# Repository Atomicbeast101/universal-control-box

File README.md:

# Universal Control Box

Kicad-designed universal control box PCB that provides the capability for end-users to quickly control various Home Assistant controls such as lights, covers, etc. The goal is to provide convenience for users to quickly make these changes without having to take out the phone to access Home Assistant app.

This design has gone through its third revision and hoping it would be the final version (updated as of 8/29/2024).

## Specifications

* Uses ESPHome to handle the turn knob and button events to trigger actions in Home Assistant.

## Schematic

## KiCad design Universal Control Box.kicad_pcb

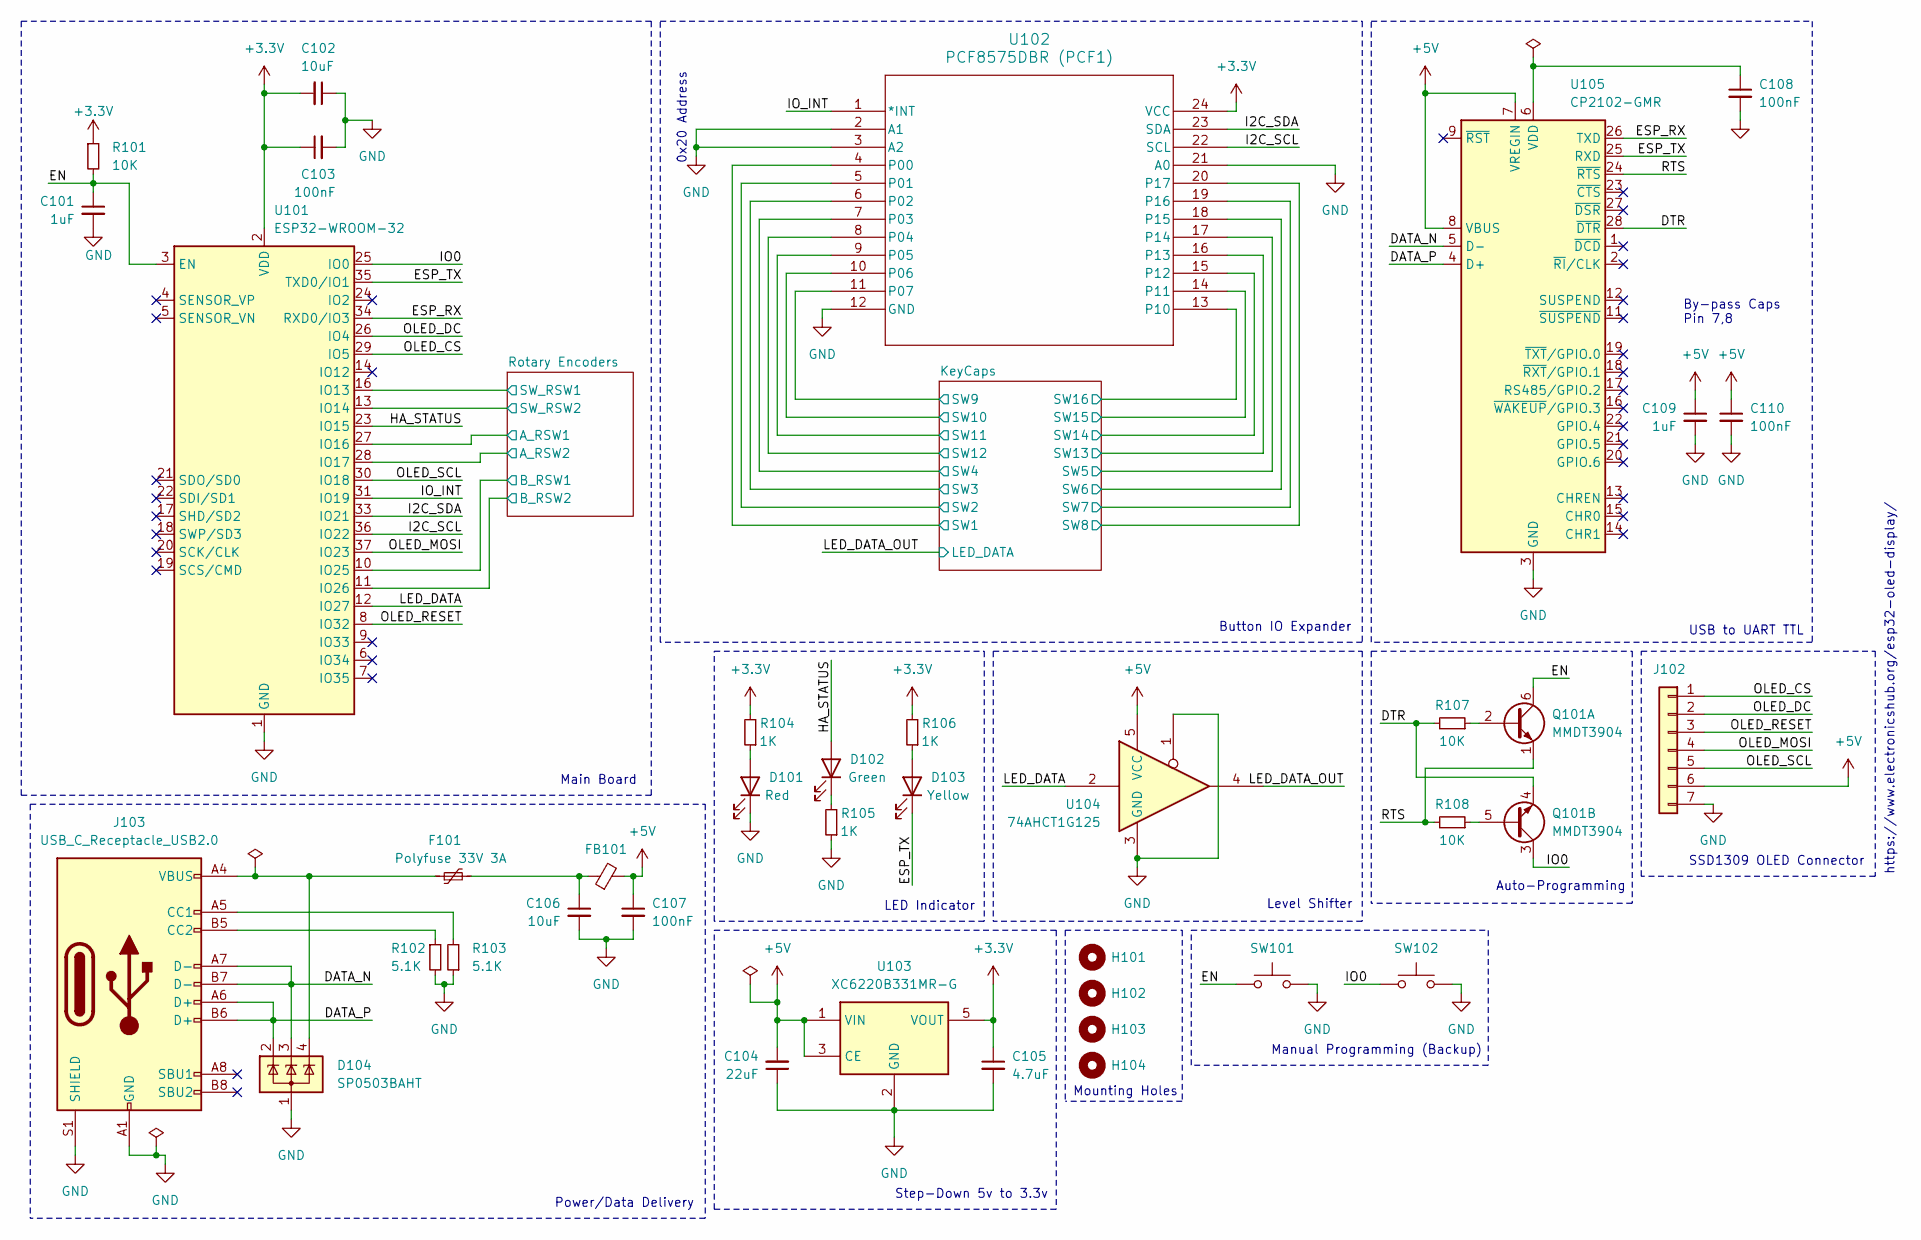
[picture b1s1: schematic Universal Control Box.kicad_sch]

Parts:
C101, C109: 1uF; C_0603_1608Metric; LCSC C14663
C102: 10uF; C_0603_1608Metric; LCSC C15850
C103, C107, C108, C110: 100nF; C_0603_1608Metric; LCSC C14663
C104: 22uF; C_0603_1608Metric; LCSC C59461
C105: 4.7uF; C_0603_1608Metric; LCSC C19666
C106: 10uF; C_0603_1608Metric; LCSC C96446
D101: Red; LED_0805_2012Metric; LCSC C84256
D102: Green; LED_0805_2012Metric; LCSC C2297
D103: Yellow; LED_0805_2012Metric; LCSC C2296
D104: SP0503BAHT; SOT-143; LCSC C7074
F101: Polyfuse 33V 3A; Fuse_1812_4532Metric; LCSC C883154
FB101: FerriteBead_Small; R_0805_2012Metric; LCSC C74487
H101, H102, H103, H104: MountingHole; MountingHole_3mm
J102: Conn_01x07; PinSocket_1x07_P2.54mm_Vertical_SSD1309
J103: USB_C_Receptacle_USB2.0; USB_C_Receptable_918-418K2023S40001; LCSC C2982555
Q101: MMDT3904; SOT-363_SC-70-6; LCSC C83572
R101, R107, R108: 10K; R_0603_1608Metric; LCSC C25804
R102, R103: 5.1K; R_0603_1608Metric; LCSC C25804
R104, R105, R106: 1K; R_0603_1608Metric; LCSC C21190
SW101, SW102: SW_Push; XKB-Connectivity-TS-1187A-B-A-B; LCSC C318884
U101: ESP32-WROOM-32; LCSC C473012
U102: PCF8575DBR (PCF1); TexasInstruments_PCF8575DBR; LCSC C2863388
U103: XC6220B331MR-G; SOT-23-5; LCSC C86534
U104: 74AHCT1G125; SOT-23-5; LCSC C7484
U105: CP2102-GMR; QFN-28-1EP_5x5mm_P0.5mm_EP3.35x3.35mm; LCSC C6568

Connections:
+3.3V: C102.2, C103.1, C105.1, R101.1, R104.2, R106.2, U101.2 (VDD), U102.24 (VCC), U103.5 (VOUT); also elsewhere on the board
+5V: C104.2, C107.1, C109.1, C110.1, FB101.2, J102.6, U103.1 (VIN), U103.3 (CE), U104.5 (VCC), U105.7 (VREGIN), U105.8 (VBUS); also elsewhere on the board
/DATA_N: D104.3 (K), J103.A7 (D-), J103.B7 (D-), U105.5 (D-)
/DATA_P: D104.2 (K), J103.A6 (D+), J103.B6 (D+), U105.4 (D+)
/DTR: Q101.4 (E2), R107.2, U105.28 (~DTR)
/EN: C101.1, Q101.6 (C1), R101.2, SW101.1, U101.3 (EN)
/ESP_RX: U101.34 (RXD0/IO3), U105.26 (TXD)
/ESP_TX: D103.1 (K), U101.35 (TXD0/IO1), U105.25 (RXD)
/HA_STATUS: D102.2 (A), U101.23 (IO15)
/I2C_SCL: U101.36 (IO22), U102.22 (SCL)
/I2C_SDA: U101.33 (IO21), U102.23 (SDA)
/IO0: Q101.3 (C2), SW102.1, U101.25 (IO0)
/IO_INT: U101.31 (IO19), U102.1 (*INT)
/KeyCaps/SW1: U102.4 (P00); also elsewhere on the board
/KeyCaps/SW2: U102.5 (P01); also elsewhere on the board
/KeyCaps/SW3: U102.6 (P02); also elsewhere on the board
/KeyCaps/SW4: U102.7 (P03); also elsewhere on the board
/KeyCaps/SW5: U102.17 (P14); also elsewhere on the board
/KeyCaps/SW6: U102.18 (P15); also elsewhere on the board
/KeyCaps/SW7: U102.19 (P16); also elsewhere on the board
/KeyCaps/SW8: U102.20 (P17); also elsewhere on the board
/KeyCaps/SW9: U102.11 (P07); also elsewhere on the board
/KeyCaps/SW10: U102.10 (P06); also elsewhere on the board
/KeyCaps/SW11: U102.9 (P05); also elsewhere on the board
/KeyCaps/SW12: U102.8 (P04); also elsewhere on the board
/KeyCaps/SW13: U102.16 (P13); also elsewhere on the board
/KeyCaps/SW14: U102.15 (P12); also elsewhere on the board
/KeyCaps/SW15: U102.14 (P11); also elsewhere on the board
/KeyCaps/SW16: U102.13 (P10); also elsewhere on the board
/LED_DATA: U101.12 (IO27), U104.2
/LED_DATA_OUT: U104.4; also elsewhere on the board
/OLED_CS: J102.1, U101.29 (IO5)
/OLED_DC: J102.2, U101.26 (IO4)
/OLED_MOSI: J102.4, U101.37 (IO23)
/OLED_RESET: J102.3, U101.8 (IO32)
/OLED_SCL: J102.5, U101.30 (IO18)
/RTS: Q101.1 (E1), R108.2, U105.24 (~RTS)
/Rotary Encoders/A_RSW1: U101.27 (IO16); also elsewhere on the board
/Rotary Encoders/A_RSW2: U101.28 (IO17); also elsewhere on the board
/Rotary Encoders/B_RSW1: U101.10 (IO25); also elsewhere on the board
/Rotary Encoders/B_RSW2: U101.11 (IO26); also elsewhere on the board
/Rotary Encoders/SW_RSW1: U101.16 (IO13); also elsewhere on the board
/Rotary Encoders/SW_RSW2: U101.13 (IO14); also elsewhere on the board
GND: C101.2, C102.1, C103.2, C104.1, C105.2, C106.2, C107.2, C108.2, C109.2, C110.2, D101.1 (K), D104.1 (A), J102.7, J103.A1 (GND), J103.A12 (GND), J103.B1 (GND), J103.B12 (GND), J103.S1 (SHIELD), R102.2, R103.1, R105.1, SW101.2, SW102.2, U101.1 (GND), U101.15 (GND), U101.38 (GND), U101.39 (GND), U102.2 (A1), U102.3 (A2), U102.12 (GND), U102.21 (A0), U103.2 (GND), U104.1, U104.3 (GND), U105.3 (GND), U105.29 (GND); also elsewhere on the board
unnamed: C106.1, F101.2, FB101.1
unnamed: D101.2 (A), R104.1
unnamed: D102.1 (K), R105.2
unnamed: D103.2 (A), R106.1
unnamed: D104.4 (K), F101.1, J103.A4 (VBUS), J103.A9 (VBUS), J103.B4 (VBUS), J103.B9 (VBUS)
unnamed: J103.A5 (CC1), R103.2
unnamed: J103.B5 (CC2), R102.1
unnamed: Q101.2 (B1), R107.1
unnamed: Q101.5 (B2), R108.1
unnamed: C108.1, U105.6 (VDD)

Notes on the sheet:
Mounting Holes
Power/Data Delivery
Button IO Expander
https://www.electronicshub.org/esp32-oled-display/
By-pass Caps Pin 7,8
Auto-Programming
LED Indicator
USB to UART TTL
0x20 Address
SSD1309 OLED Connector
Manual Programming (Backup)
Step-Down 5v to 3.3v
Level Shifter
Main Board

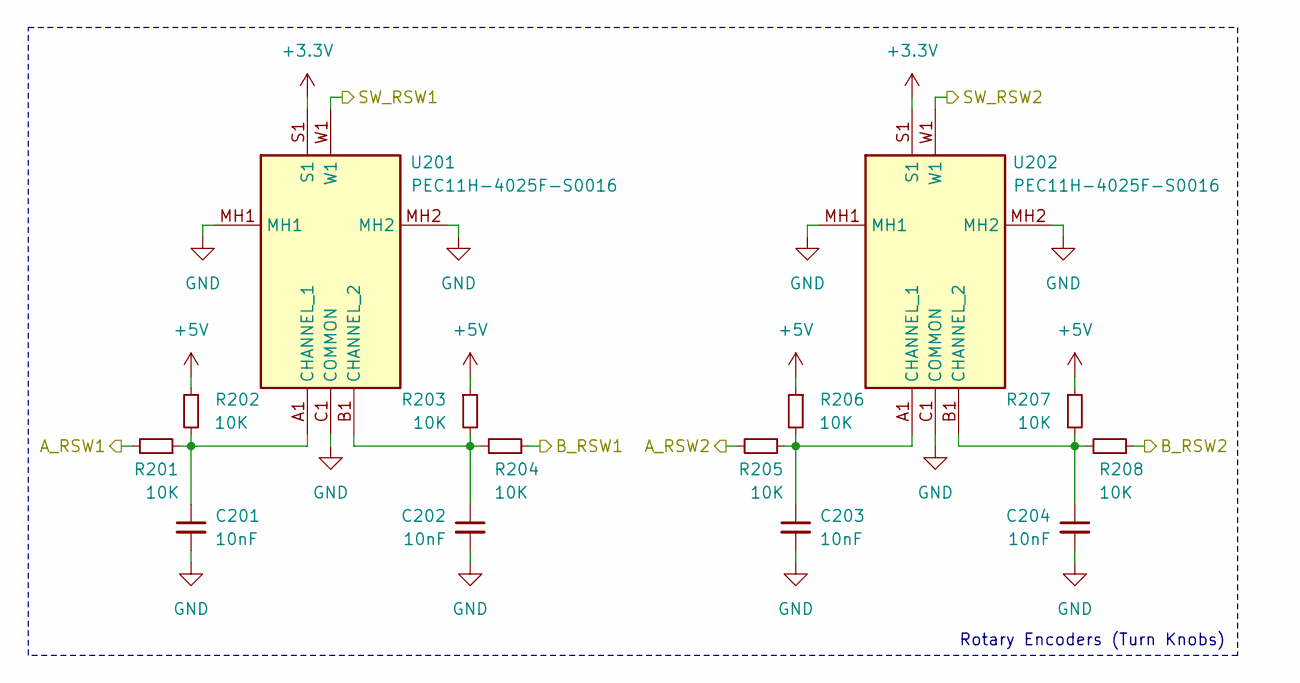
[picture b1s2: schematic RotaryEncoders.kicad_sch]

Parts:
C201, C202, C203, C204: 10nF; C_0603_1608Metric; LCSC C57112
R201, R202, R203, R204, R205, R206, R207, R208: 10K; R_0603_1608Metric; LCSC C25804
U201, U202: PEC11H-4025F-S0016; PEC11H4025FS0016; Mouser Part Number 652-PEC11H4025FS0016

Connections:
+3.3V: U201.S1, U202.S1; also elsewhere on the board
+5V: R202.1, R203.1, R206.1, R207.1; also elsewhere on the board
/Rotary Encoders/A_RSW1: R201.2; also elsewhere on the board
/Rotary Encoders/A_RSW2: R205.2; also elsewhere on the board
/Rotary Encoders/B_RSW1: R204.1; also elsewhere on the board
/Rotary Encoders/B_RSW2: R208.1; also elsewhere on the board
/Rotary Encoders/SW_RSW1: U201.W1; also elsewhere on the board
/Rotary Encoders/SW_RSW2: U202.W1; also elsewhere on the board
GND: C201.2, C202.2, C203.2, C204.2, U201.C1 (COMMON), U201.MH1, U201.MH2, U202.C1 (COMMON), U202.MH1, U202.MH2; also elsewhere on the board
unnamed: C201.1, R201.1, R202.2, U201.A1 (CHANNEL_1)
unnamed: C202.1, R203.2, R204.2, U201.B1 (CHANNEL_2)
unnamed: C203.1, R205.1, R206.2, U202.A1 (CHANNEL_1)
unnamed: C204.1, R207.2, R208.2, U202.B1 (CHANNEL_2)

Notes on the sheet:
Rotary Encoders (Turn Knobs)

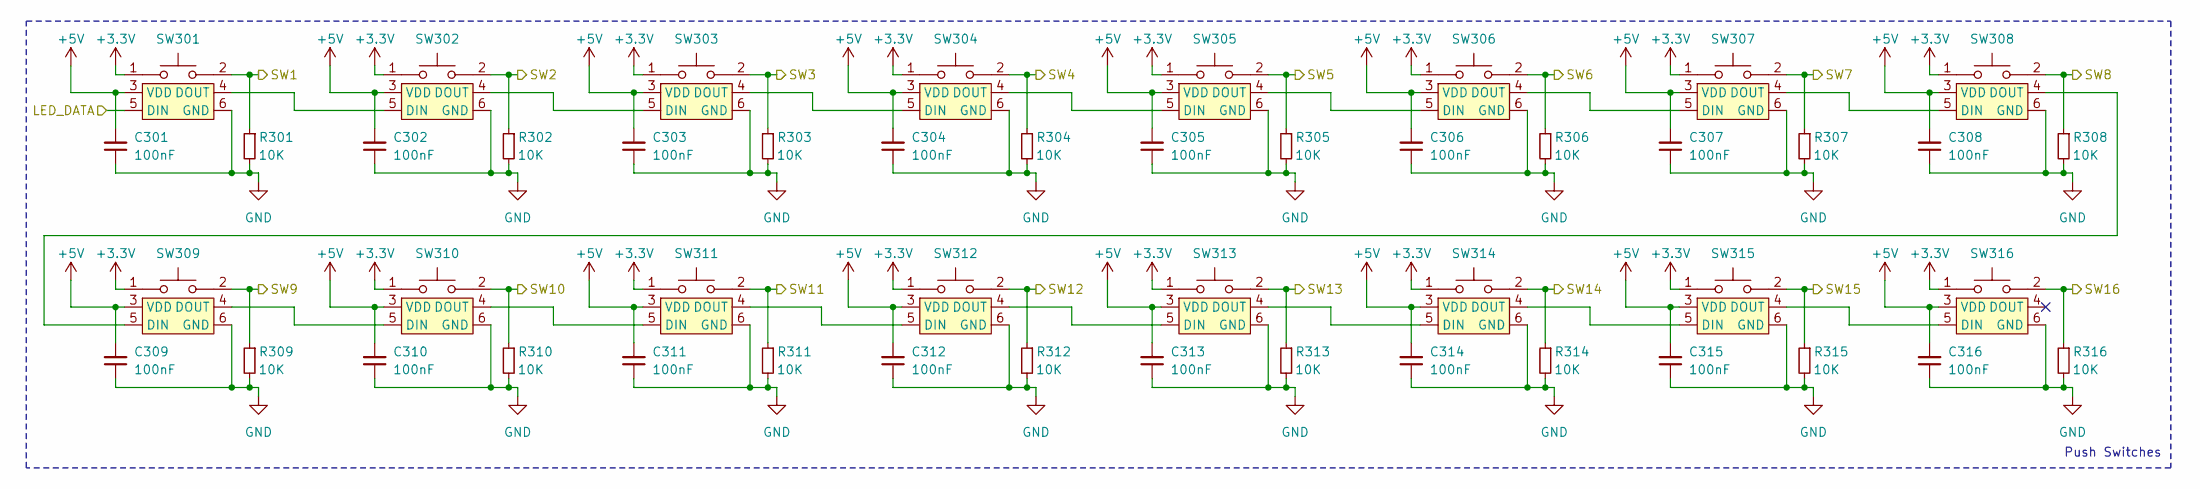
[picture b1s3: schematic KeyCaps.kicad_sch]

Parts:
C301, C302, C303, C304, C305, C306, C307, C308, C309, C310, C311, C312, C313, C314, C315, C316: 100nF; C_0603_1608Metric; LCSC C14663
R301, R302, R303, R304, R305, R306, R307, R308, R309, R310, R311, R312, R313, R314, R315, R316: 10K; R_0603_1608Metric; LCSC C25804
SW301, SW302, SW303, SW304, SW305, SW306, SW307, SW308, SW309, SW310, SW311, SW312, SW313, SW314, SW315, SW316: CherryMX_1.00u_PCB_WS2812B-2020; LCSC C965555

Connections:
+3.3V: SW301.1, SW302.1, SW303.1, SW304.1, SW305.1, SW306.1, SW307.1, SW308.1, SW309.1, SW310.1, SW311.1, SW312.1, SW313.1, SW314.1, SW315.1, SW316.1; also elsewhere on the board
+5V: C301.2, C302.2, C303.2, C304.2, C305.2, C306.2, C307.2, C308.2, C309.2, C310.2, C311.2, C312.2, C313.2, C314.2, C315.2, C316.2, SW301.3 (VDD), SW302.3 (VDD), SW303.3 (VDD), SW304.3 (VDD), SW305.3 (VDD), SW306.3 (VDD), SW307.3 (VDD), SW308.3 (VDD), SW309.3 (VDD), SW310.3 (VDD), SW311.3 (VDD), SW312.3 (VDD), SW313.3 (VDD), SW314.3 (VDD), SW315.3 (VDD), SW316.3 (VDD); also elsewhere on the board
/KeyCaps/SW1: R301.1, SW301.2; also elsewhere on the board
/KeyCaps/SW2: R302.1, SW302.2; also elsewhere on the board
/KeyCaps/SW3: R303.1, SW303.2; also elsewhere on the board
/KeyCaps/SW4: R304.1, SW304.2; also elsewhere on the board
/KeyCaps/SW5: R305.1, SW305.2; also elsewhere on the board
/KeyCaps/SW6: R306.1, SW306.2; also elsewhere on the board
/KeyCaps/SW7: R307.1, SW307.2; also elsewhere on the board
/KeyCaps/SW8: R308.1, SW308.2; also elsewhere on the board
/KeyCaps/SW9: R309.1, SW309.2; also elsewhere on the board
/KeyCaps/SW10: R310.1, SW310.2; also elsewhere on the board
/KeyCaps/SW11: R311.1, SW311.2; also elsewhere on the board
/KeyCaps/SW12: R312.1, SW312.2; also elsewhere on the board
/KeyCaps/SW13: R313.1, SW313.2; also elsewhere on the board
/KeyCaps/SW14: R314.1, SW314.2; also elsewhere on the board
/KeyCaps/SW15: R315.1, SW315.2; also elsewhere on the board
/KeyCaps/SW16: R316.1, SW316.2; also elsewhere on the board
/LED_DATA_OUT: SW301.5 (DIN); also elsewhere on the board
GND: C301.1, C302.1, C303.1, C304.1, C305.1, C306.1, C307.1, C308.1, C309.1, C310.1, C311.1, C312.1, C313.1, C314.1, C315.1, C316.1, R301.2, R302.2, R303.2, R304.2, R305.2, R306.2, R307.2, R308.2, R309.2, R310.2, R311.2, R312.2, R313.2, R314.2, R315.2, R316.2, SW301.6 (GND), SW302.6 (GND), SW303.6 (GND), SW304.6 (GND), SW305.6 (GND), SW306.6 (GND), SW307.6 (GND), SW308.6 (GND), SW309.6 (GND), SW310.6 (GND), SW311.6 (GND), SW312.6 (GND), SW313.6 (GND), SW314.6 (GND), SW315.6 (GND), SW316.6 (GND); also elsewhere on the board
unnamed: SW301.4 (DOUT), SW302.5 (DIN)
unnamed: SW302.4 (DOUT), SW303.5 (DIN)
unnamed: SW303.4 (DOUT), SW304.5 (DIN)
unnamed: SW304.4 (DOUT), SW305.5 (DIN)
unnamed: SW305.4 (DOUT), SW306.5 (DIN)
unnamed: SW306.4 (DOUT), SW307.5 (DIN)
unnamed: SW307.4 (DOUT), SW308.5 (DIN)
unnamed: SW308.4 (DOUT), SW309.5 (DIN)
unnamed: SW309.4 (DOUT), SW310.5 (DIN)
unnamed: SW310.4 (DOUT), SW311.5 (DIN)
unnamed: SW311.4 (DOUT), SW312.5 (DIN)
unnamed: SW312.4 (DOUT), SW313.5 (DIN)
unnamed: SW313.4 (DOUT), SW314.5 (DIN)
unnamed: SW314.4 (DOUT), SW315.5 (DIN)
unnamed: SW315.4 (DOUT), SW316.5 (DIN)

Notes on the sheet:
Push Switches

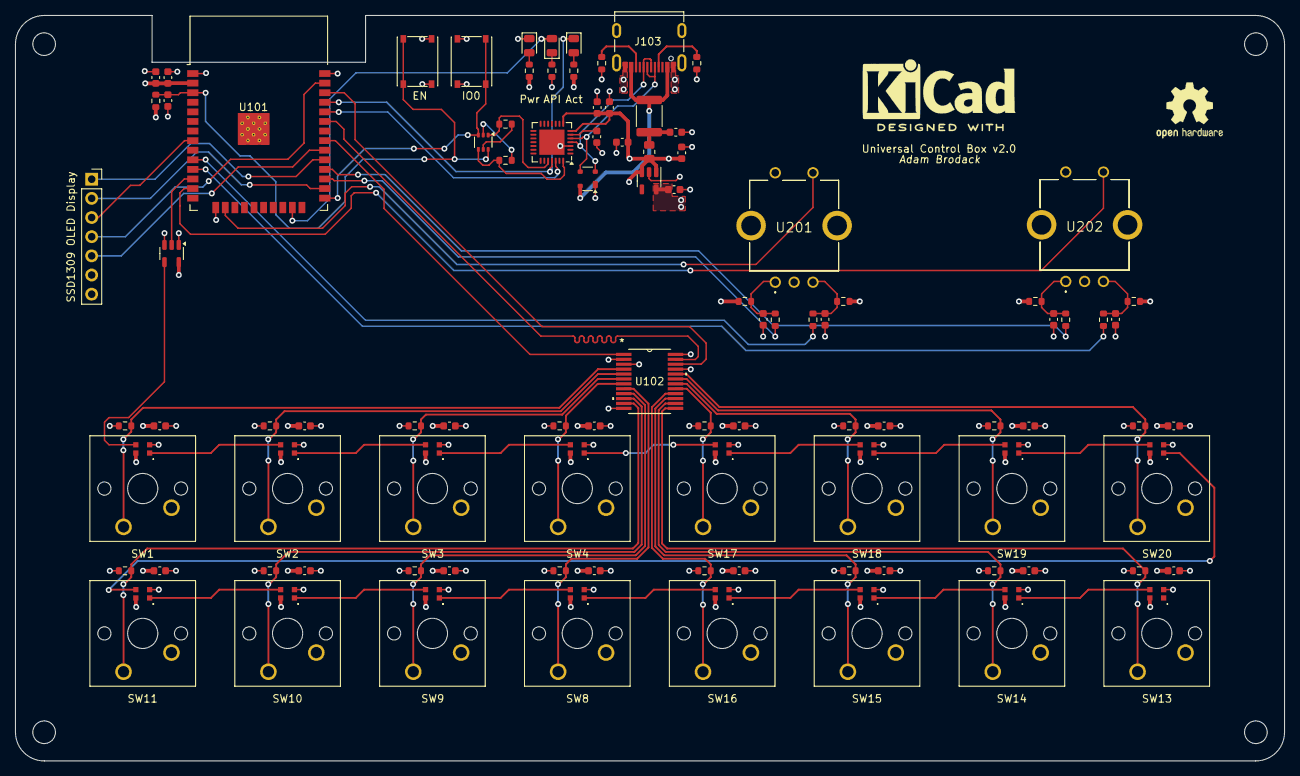
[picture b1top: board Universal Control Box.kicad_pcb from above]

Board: 4 copper layers, 168.2 x 98.8 mm, 100 parts (0 on the bottom side), 73 nets.

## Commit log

2024-01-10 Create .gitignore
    Added .gitignore
2024-01-17 Major changes
2024-01-19 add design review comments
2024-01-20 Fixed wiring for buttons
2024-01-26 Made changes based on Josh's comments & switched to Switched to WS2812B-2020
2024-01-27 Fixed LED Schematic & added 2 more LEDs
2024-01-27 Added missing resistor for Green LED
2024-01-27 Updated PCB layout (no wires yet)
2024-03-14 Added GND & other stuff
2024-03-16 Added remaining traces
2024-03-16 suggested changes
2024-03-17 update net colors
2024-04-26 Updated designs to meet feedback
2024-04-27 Some improvements & added labeling
2024-04-28 Included symbols/footprints/3dmodels to repo
2024-04-28 Fixed library links
2024-04-28 add keycap model
2024-04-28 add pcb 3d model
2024-04-28 update design
2024-05-05 Fixes
2024-05-05 Updated keycap & added missing logos
2024-05-05 Fixed trace route length for I2C
2024-05-06 Remove jlcpcb files
2024-05-07 Fix logo stuff
2024-05-18 Updated 3d model
2024-05-19 Fixed origin position for exported .step file
2024-05-21 add nclosure models
2024-06-04 Fixed wiring for OLED display, push button for rotary & added chips for programming via USB C
2024-06-05 Organized overview a little bit
2024-06-05 A few more improvements
2024-06-05 Even more layout improvements
2024-06-08 added comments
2024-06-08 Fixed part #s & switched TX & RX
2024-06-08 Removed old notes
2024-06-18 Updated PCB to include USB based RX/TX
2024-06-19 minor fixes
    - moved some tracks
    - vias to each ground pads
2024-06-20 Fixed GND positions & LCSC part for dual mosfet
2024-06-20 Minor fixes - ready for order
2024-06-20 Fixed to include WS2812B-2020 part
2024-07-04 revised some traces
2024-08-31 Added README & created v2.1 branch (copied from josh's feedback branch)
